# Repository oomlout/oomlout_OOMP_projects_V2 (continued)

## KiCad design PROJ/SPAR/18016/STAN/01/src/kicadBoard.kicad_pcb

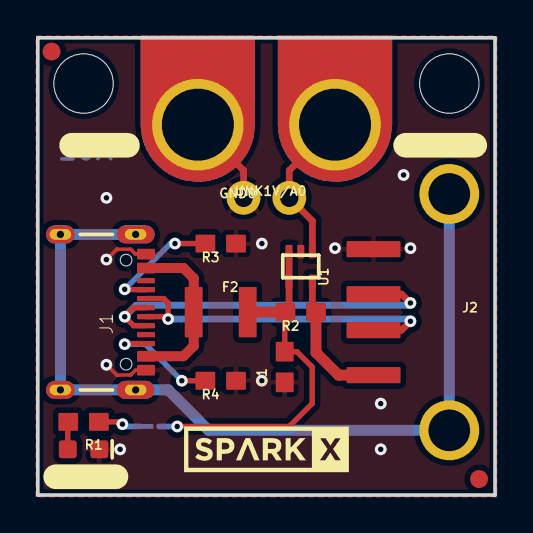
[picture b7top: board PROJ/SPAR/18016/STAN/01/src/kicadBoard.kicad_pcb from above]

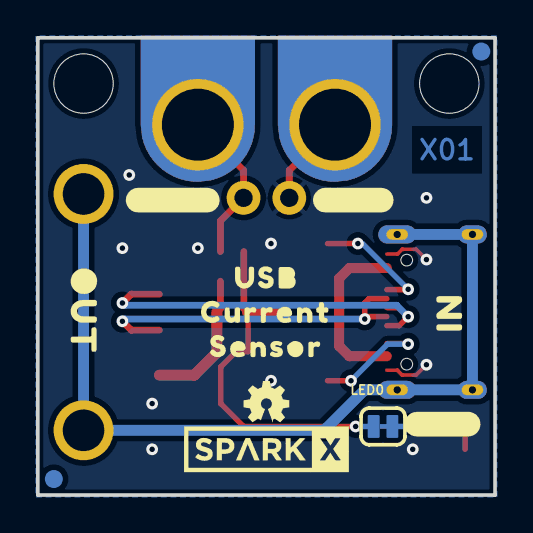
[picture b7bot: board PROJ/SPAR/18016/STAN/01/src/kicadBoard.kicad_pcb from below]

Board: 2 copper layers, 25.4 x 25.4 mm, 37 parts (13 on the bottom side), 12 nets.

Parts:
C1: 0.1uF; 0603
D1: RED; LED-0603
F2: 6V/2A; 1210
FRAME1: FRAME-LETTER; CREATIVE_COMMONS
GND0: 1X01_NO_SILK
J1: USB-C-16P_4LAYER-PADS
J2: USB_A_FEMALE; USB-A-S-NOSILK-FEMALE
J3, J4: TAB_GATOR_MINI
JP1, JP2, JP5, JP6: FIDUCIAL1X2; FIDUCIAL-1X2
JP3, JP4: STAND-OFF
LED0: SMT-JUMPER_2_NC_TRACE_SILK
LOGO1: OSHW-LOGOMINI; OSHW-LOGO-MINI
LOGO2: SPECIAL_INSTRUCTIONS-ORDERING; ORDERING_INSTRUCTIONS
R1: 2.2k; 0603
R2: 0.05; 0603
R3, R4: 5.1k; 0603
U1: INA290A1(20V/V); SC70
U$1, U$2: SPARKX-LOGO4; SPARKX-MEDIUM
U$3, U$4: #GND#0
U$5, U$6: #1V#A#0
U$7: USB0
U$8: CURRENT0
U$9: SENSOR0
U$10: IN0
U$11: OUT0
U$13: #PWR#0
U$14: #LED#0
UNK1V/A0: 1X01_NO_SILK

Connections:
1V/A: J3.P1, U1.1, UNK1V/A0.1
5V: C1.1, F2.2, LED0.2, R2.2, U1.3, U1.4
GND: C1.2, D1.C, GND0.1, J1.GND, J1.GND2, J2.GND, J4.P1, R3.1, R4.1, U1.2
unnamed: D1.A, R1.1
unnamed: LED0.1, R1.2
unnamed: J1.A5, R3.2
unnamed: J1.B5, R4.2
unnamed: F2.1, J1.VBUS1, J1.VBUS2
SHLD: J1.SHLD1, J1.SHLD2, J1.SHLD3, J1.SHLD4, J2.SHLD1, J2.SHLD2
USB_D+: J1.A6, J1.B6, J2.D+
USB_D-: J1.A7, J1.B7, J2.D-
VOUT: J2.VBUS, R2.1, U1.5

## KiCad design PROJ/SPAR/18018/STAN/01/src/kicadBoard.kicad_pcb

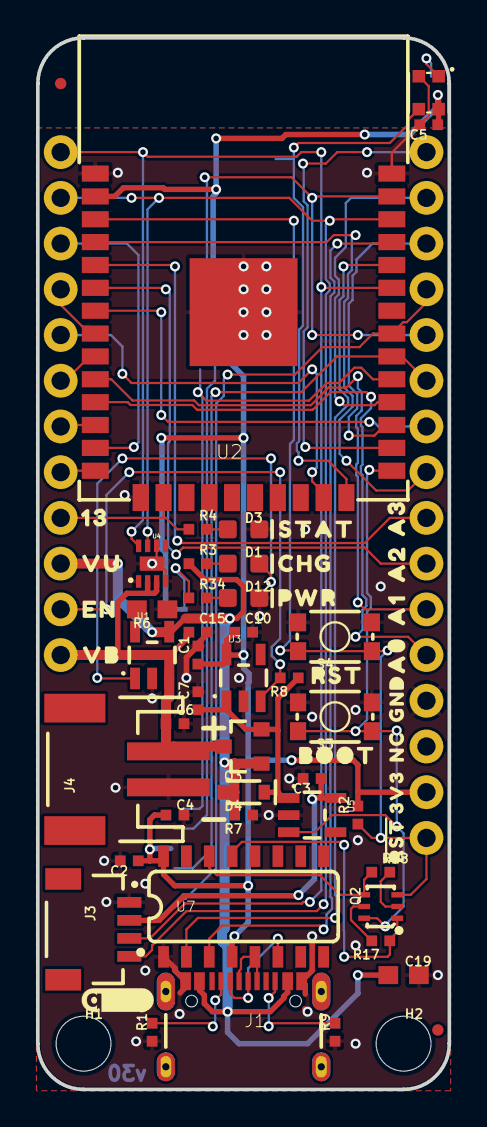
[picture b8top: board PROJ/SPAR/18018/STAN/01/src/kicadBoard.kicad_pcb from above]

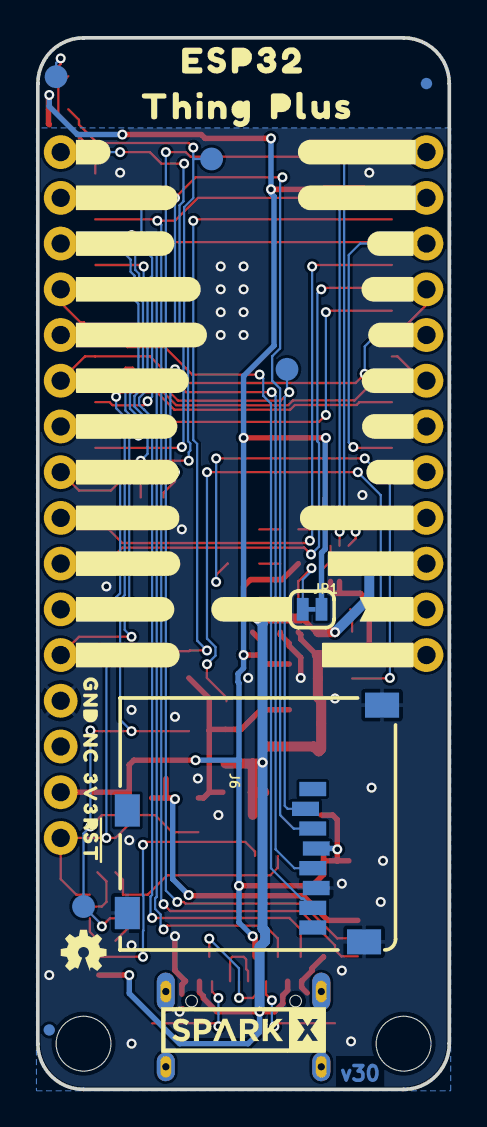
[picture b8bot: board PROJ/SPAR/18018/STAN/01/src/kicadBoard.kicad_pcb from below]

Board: 2 copper layers, 22.9 x 58.4 mm, 106 parts (42 on the bottom side), 49 nets.

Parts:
C1: 10uF; 0402-TIGHT
C2, C4, C5, C15: 0.1uF; 0402-TIGHT
C3, C7, C10: 1.0uF; 0402-TIGHT
C6: 4.7uF; 0402-TIGHT
C19: 4.7uF; 0603
D1: Yellow; LED-0603
D3: BLUE; LED-0603
D4: 3A/10V/280mV; SOD-323
D5: WS2812; WS2812-2020
D12: RED; LED-0603
FD1, FD2, FD3, FD4: FIDUCIALUFIDUCIAL; FIDUCIAL-MICRO
FRAME1: FRAME-LEDGER; CREATIVE_COMMONS
H1, H2: STAND-OFFTIGHT; STAND-OFF-TIGHT
J1: USB-C-16P-2LAYER-PADS
J3: QWIIC_RIGHT_ANGLE; JST04_1MM_RA
J4: JST-2-SMD
J6: microSD; MICRO-SD-SOCKET
JP1: SMT-JUMPER_2_NC_TRACE_SILK
LOGO2: OSHW-LOGOMINI; OSHW-LOGO-MINI
LOGO4: QWIIC_LOGO_4MM; QWIIC_4MM
Q2: MBT3904DW1T1; SC70-6
Q3: 20V/4.2A/52mΩ/1.4W; SOT23-3
R2, R7, R8, R17, R18: 10k; 0402-TIGHT
R3, R4, R34: 1k; 0402-TIGHT
R6: 2.0k; 0603
R9, R10: 5.1k; 0402-TIGHT
S3: Boot; TACTILE_SWITCH_SMD_4.6X2.8MM
S4: Reset; TACTILE_SWITCH_SMD_4.6X2.8MM
TP1, TP2, TP3, TP4: PAD.03X.05
U1: MCP73831; SOT23-5
U2: ESP-WROOM-32NARROW; ESP-WROOM-32-NARROW
U3, U5: AP2112K-3.3; SOT23-5
U4: MAX17048; DFN-8
U6: THINGPLUS_LOGICAL; THINGPLUS_FOOTPRINT
U7: CH340C; SO016
U$1: SPARKX-LOGO4; SPARKX-MEDIUM
U$23, U$108: 3V30
U$24: CHG1
U$25: PWR2
U$26: STAT0
U$56, U$75: GND1
U$57: #4#0
U$59: ORDERING_INSTRUCTIONS
U$62: #23#COPI#0
U$68: A03
U$69: A12
U$70: A21
U$71: A30
U$72: #17#TX#0
U$73: VB1
U$74: EN3
U$76: VU0
U$77: 130
U$78: BOOT0
U$79, U$109: #RST#0
U$80: RST0
U$81: #16#RX#0
U$82: #19#CIPO#0
U$83: #18#SCK#0
U$84: #35#A5#0
U$85: #36#A4#0
U$86: #25#A1#2
U$87: #26#A0#3
U$88: #34#A2#1
U$89: #39#A3#0
U$90: #12#4
U$91: #14#9
U$92: #15#7
U$93: #27#5
U$94: #32#8
U$95: #33#6
U$96: #EN#1
U$97: #VBAT#0
U$98: #VUSB#2
U$99: #13#LED#0
U$100: #21#SDA#1
U$101: #22#SCL#0
U$102: #PWR#0
U$103: ESP320
U$104: THING1
U$105: PLUS2
U$106, U$107: NC0

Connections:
3.3V: C1.1, C2.1, C4.1, C5.1, C10.1, D5.VCC, J6.VCC, JP1.2, R2.2, U2.2, U3.5, U6.3V3, U7.4, U7.16
CH340-DTR: Q2.1, R17.1, U7.13
CH340-RTS: Q2.4, R18.1, U7.14
CH340-RX: U2.35, U7.3
CH340-TX: U2.34, U7.2
CHG: D1.C, U1.1
CHG_LED: D1.A, R3.2
D+: J1.A6, J1.B6, U7.5
D-: J1.A7, J1.B7, U7.6
DTR-10K: Q2.5, R17.2
ESP_0/QPWR: Q2.6, S3.3, S3.4, TP1.P$1, U2.25, U5.3
ESP_2/RGB_DI: D5.DI, TP3.P$1, U2.24
ESP_4/TP_FB: U2.26, U6.FREEBIE
ESP_5/SD_CS: J6.CS/DAT3, TP4.P$1, U2.29
ESP_12/TP_12: U2.14, U6.12
ESP_13/TP_13/LED: R4.1, U2.16, U6.13
ESP_14/TP_7: U2.13, U6.7
ESP_15/TP_9: U2.23, U6.9
ESP_16/TP_RX: U2.27, U6.RX
ESP_17/TP_TX: U2.28, U6.TX
ESP_18/TP_SCK: J6.SCLK, U2.30, U6.SCK
ESP_19/TP_CIPO: J6.DO/DAT0, U2.31, U6.CIPO
ESP_21/TP_SDA: J3.3, U2.33, U4.8, U6.SDA
ESP_22/TP_SCL: J3.4, U2.36, U4.7, U6.SCL
ESP_23/TP_COPI: J6.DI/CMD, U2.37, U6.COPI
ESP_25/TP_A1: U2.10, U6.A1
ESP_26/TP_A0: U2.11, U6.A0
ESP_27/TP_11: U2.12, U6.11
ESP_32/TP_8: U2.8, U6.8
ESP_33/TP_10: U2.9, U6.10
ESP_34/TP_A2: U2.6, U6.A2
ESP_35/TP_A5: U2.7, U6.A5
ESP_36/TP_A4: U2.4, U6.A4
ESP_39/TP_A3: U2.5, U6.A3
GND: C1.2, C2.2, C3.2, C4.2, C5.2, C6.2, C7.2, C10.2, C15.2, C19.2, D3.C, D5.GND, D12.C, J1.GND, J1.GND2, J3.1, J4.1, J6.CD1, J6.GND, J6.GND1, J6.GND3, R6.1, R7.1, R9.1, R10.1, S3.1, S3.2, S4.1, S4.2, U1.2, U2.1, U2.15, U2.38, U2.GND, U3.2, U4.1, U4.4, U4.6, U4.9, U5.2, U6.GND, U7.1
unnamed: JP1.1, R34.1
unnamed: D3.A, R4.2
unnamed: D5.DO, TP2.P$1
unnamed: J1.B5, R9.2
unnamed: J1.A5, R10.2
unnamed: R6.2, U1.5
unnamed: D12.A, R34.2
QWIIC_PWR: C3.1, J3.2, U5.5
RTS-10K: Q2.2, R18.2
TP_EN: R8.2, U3.3, U6.EN
VIN: C7.1, D4.C, Q3.2, R8.1, U3.1, U5.1
V_BATT: C6.1, C15.1, J4.2, Q3.3, U1.3, U4.2, U4.3, U6.V_BATT
V_USB: C19.1, D4.A, J1.VBUS1, J1.VBUS2, Q3.1, R3.1, R7.2, U1.4, U6.V_USB
~RESET: Q2.3, R2.1, S4.3, S4.4, U2.3, U6.RST
